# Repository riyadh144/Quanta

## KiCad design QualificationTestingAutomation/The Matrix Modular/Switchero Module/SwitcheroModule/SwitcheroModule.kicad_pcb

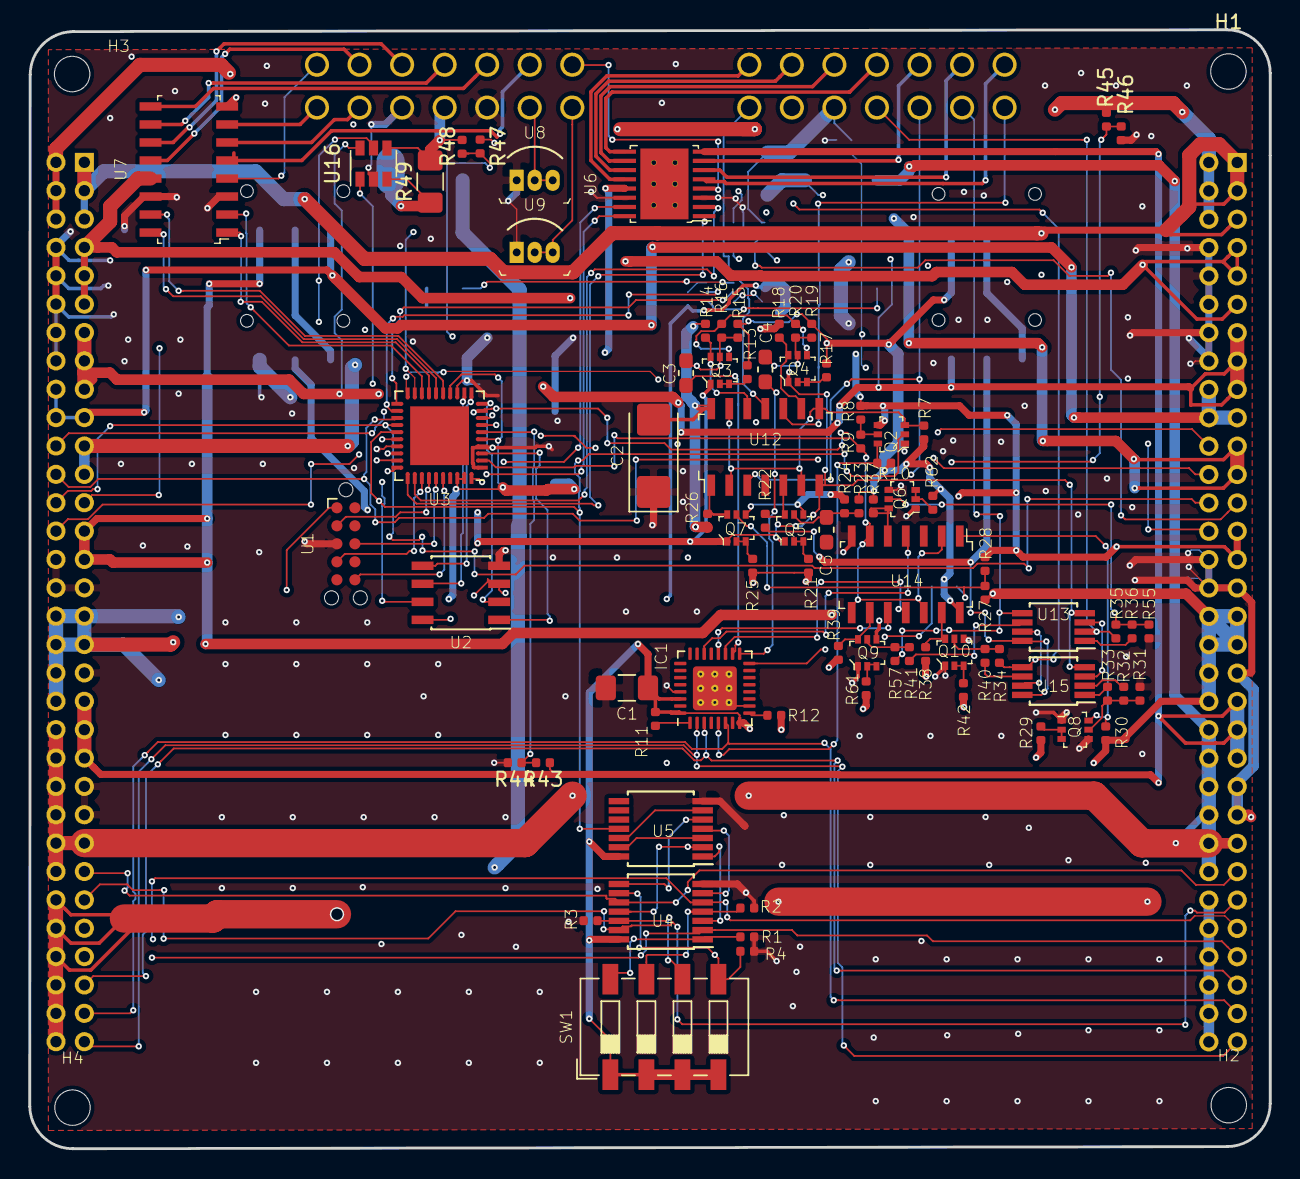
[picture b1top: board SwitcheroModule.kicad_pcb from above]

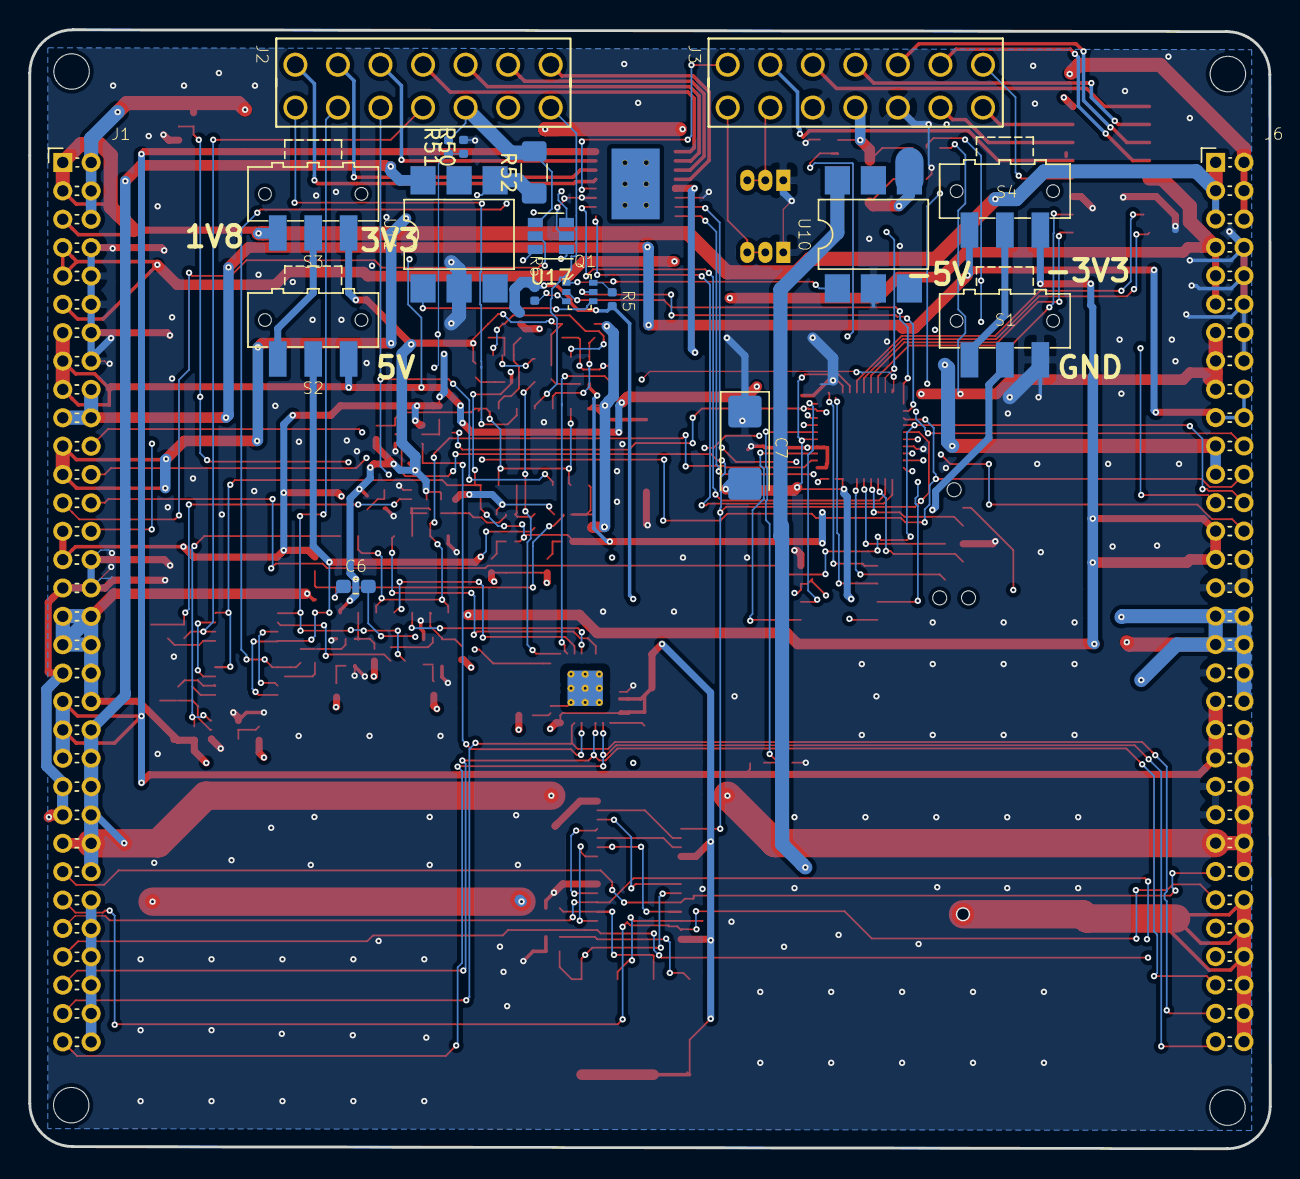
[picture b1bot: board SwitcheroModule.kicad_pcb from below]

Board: 4 copper layers, 87.5 x 78.9 mm, 104 parts (19 on the bottom side), 139 nets.

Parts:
C1: .1uF; C_1206_3216Metric_Pad1.42x1.75mm_HandSolder
C2, C7: 1uF; CP_EIA-6032-15_Kemet-U_Pad2.25x2.35mm_HandSolder
C3, C4, C5, C6: 1uF; C_0603_1608Metric_Pad1.05x0.95mm_HandSolder
H1, H2, H3, H4: MountingHole; MountingHole_2.5mm
IC1: MAX3109ETJ+; QFN-32-1EP_5x5mm_P0.5mm_EP3.1x3.1mm_ThermalVias
J1, J6: Conn_02x32_Counter_Clockwise_MountingPin; PinHeader_2x32_P2.00mm_VerticalOpp
J2, J3: OBD Connector; 3MM
Q1, Q2, Q3, Q4, Q5, Q6, Q7, Q8, Q9, Q10: 2N7002DW; SOT-363
R1, R2, R3, R4, R29, R30, R37, R38, R39, R42, R45, R61, R62: 100k; R_0402_1005Metric
R5, R6: 8K; R_0402_1005Metric
R7, R8, R9, R10, R12: 100K; R_0402_1005Metric
R11: 10K; R_0402_1005Metric
R13, R17, R21, R25: 15K; R_0402_1005Metric
R14, R18, R22, R26: 15k; R_0402_1005Metric
R15, R16, R19, R20, R23, R24, R27, R28: 200K; R_0402_1005Metric
R31, R55: RESISTOR; R_0402_1005Metric
R32, R33, R34, R35, R36, R40, R41, R57: R0; R_0402_1005Metric
R43, R48, R51: 1meg; R_0402_1005Metric
R44, R47, R50: 40K; R_0402_1005Metric
R46: 23.8K; R_0402_1005Metric
R49, R52: .02; R_1206_3216Metric_Pad1.42x1.75mm_HandSolder
S1, S2, S3, S4: ATE1D-2M3-10-Z; SW_SPDT_CK-JS102011SAQN
SW1: SW_DIP_x04; SW_DIP_SPSTx04_Slide_6.7x11.72mm_W6.73mm_P2.54mm_LowProfile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
U1: TC2050-JTAG-SchematicAutomation-rescue; Tag-Connect_TC2050-IDC-NL_2x05_P1.27mm_Vertical
U2: AT25SF081-SSHD-X; SOIC-8_3.9x4.9mm_P1.27mm
U3: MSP430G2755IRHA40; Texas_S-PVQFN-N40_EP4.15x4.15mm
U4: SN74HC266DR; TSSOP-14_4.4x5mm_P0.65mm
U5: SN74LVC08APWR; TSSOP-14_4.4x5mm_P0.65mm
U6: MAX14752; TSSOP-16-1EP_W4.40mm
U7: DG408LE; SOIC-16_W3.90mm
U8, U9: DS18B20_; TO-92-3
U10, U11: TLP3546; SMDIP-6_W7.62mm
U12, U14: CD4070B; SOIC-14_W3.9mm
U13, U15: MAX324CUA; MSOP-8_3x3mm_P0.65mm
U16, U17: INA181; SOT-23-6

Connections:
1.25V: J1.25, J6.25, U16.5, U17.5
1_ADC0: J3.14, U6.4
1_ADC1: J2.12, U6.7
1_ADC2: J2.13, U6.6
1_ADC3: J2.14, U6.5
1_CTS: J2.3, U12.3
1_GarminPWR: J2.5, R51.2, R52.2, U17.4
1_GarminRX: J2.6, R34.1, U15.5
1_GarminTX: J2.7, U12.11
1_IN0: J2.8, U6.12
1_IN1: J2.9, U6.11
1_IN2: J2.10, U6.10
1_IN3: J2.11, U6.9
1_OUT0: J3.8, U7.4
1_OUT1: J3.13, U7.5
1_OUT2: J3.6, U7.6
1_OUT3: J3.7, U7.7
1_OWB_PRI: J3.2, U8.2, U8.3
1_OWB_SEC: J3.1, U9.2, U9.3
1_RTS: J2.4, R35.2, U13.2
1_RX: J2.2, R57.1, U13.5
1_TX: J2.1, U12.10
1_Vin: J3.4, R48.2, R49.2, U16.4
2_OUT0: J3.9, U7.12
2_OUT1: J3.10, U7.11
2_OUT2: J3.11, U7.10
2_OUT3: J3.12, U7.9
+1V8: J1.1, J1.3, J1.5, J6.1, J6.3, J6.5, S3.3
+2V5: J1.28, J6.28, U3.28
+3V3: C1.1, C7.2, IC1.8, IC1.30, IC1.32, J1.33, J1.34, J1.35, J1.36, J1.38, J1.40, J6.33, J6.34, J6.35, J6.36, J6.38, J6.40, R5.1, R6.1, R7.1, R10.1, R11.2, R12.2, R13.1, R15.1, R17.1, R19.1, R21.1, R23.1, R25.1, R27.1, R29.1, R30.2, R37.2, R38.2, R39.2, R42.1, R61.1, R62.1, S3.1, SW1.1, SW1.2, SW1.3, SW1.4, U1.1, U2.3, U2.8, U3.5, U3.14, U3.38, U3.39, U4.14, U5.14, U14.14
+5V: J1.13, J1.15, J1.17, J6.13, J6.15, J6.17, S2.1, U16.6, U17.6
+12V: J1.7, J1.9, J1.11, J6.7, J6.9, J6.11, U7.13
+VSW: C2.2, R14.2, R18.2, R22.2, R26.2, S2.2, U12.14, U13.8, U15.8
-3V3: J1.27, J1.29, J6.27, J6.29, Q2.4, Q3.4, Q4.4, Q5.4, Q7.4, R8.2, R16.2, R20.2, R24.2, R28.2, S4.1
-5V: J1.18, J1.19, J1.20, J6.18, J6.19, J6.20, S4.3
-VSW: Q3.1, Q4.1, Q5.1, Q7.1, S1.2, U12.7, U13.4, U15.4
/Micro/CSB: U2.1, U3.3
/Micro/SCKB: U2.6, U3.12
/Micro/SIMOB: U2.5, U3.11
/Micro/SOMIB: U2.2, U3.10
/Micro/TCK: U1.4, U3.33
/Micro/TDI: U1.8, U3.35
/Micro/TDO: U1.6, U3.36
/Micro/TMS: U1.2, U3.34
/Micro/\HOLD: U2.7, U3.40
/Serial/RX/Sheet5CA21CAA/TX_+3v3-3v3: Q3.6, R14.1, U12.12
/Serial/RX/TX_3v3_1: C3.2, IC1.18
/Serial/RX/TX_3v3_2: C4.2, IC1.17
/Serial/RX/TX_3v3_3: C6.2, IC1.16
/Serial/RX/sheet5CA23CF1/TX_+3v3-3v3: Q4.6, R18.1, U12.9
/Serial/RX/sheet5CA2401A/TX_+3v3-3v3: Q5.6, R22.1, U12.5
/Serial/RX/sheet5CA24179/TX_+3v3-3v3: Q7.6, R26.1, U12.1
/Serial/sheet5C94ECE6/RX_1: R32.2, U15.2
/Serial/sheet5C94ECE6/RX_3V3_2: IC1.22, U14.4
/Serial/sheet5C94ECE6/RX_3V3_3: IC1.20, U14.10
/Serial/sheet5C94ECE6/RX_3V3_4: IC1.19, U14.11
CTS_CONT: U13.3, U15.3
GND: C1.2, C2.1, C7.1, IC1.10, IC1.29, IC1.33, J1.8, J1.10, J1.12, J1.14, J1.16, J1.30, J1.31, J1.32, J1.37, J1.45, J1.47, J3.3, J3.5, J6.8, J6.10, J6.12, J6.14, J6.16, J6.30, J6.31, J6.32, J6.37, J6.45, J6.47, Q2.1, Q6.1, Q6.4, Q8.1, Q8.4, Q9.1, Q9.4, Q10.1, Q10.4, R1.2, R2.2, R3.2, R4.2, R31.2, R44.2, R46.2, R47.2, R50.2, R55.2, S1.1, U1.3, U2.4, U3.1, U3.4, U3.13, U3.27, U4.7, U5.7, U6.3, U6.14, U7.3, U7.14, U8.1, U9.1, U10.2, U11.2, U14.7, U16.2, U17.2
HT: J1.21, J1.23, J6.21, J6.23, U6.13
IADC_Garmin: U3.19, U17.1
IADC_Vin: U3.8, U16.1
LO: J1.2, J1.4, J1.6, J6.2, J6.4, J6.6, R45.1, U7.8
MISO0: J1.24, J6.24, U3.23
MISO1: IC1.2, J1.63, J6.63
MOSI0: J1.26, J6.26, U3.24
MOSI1: IC1.6, J1.61, J6.61
MSP_MUX1_EN: U3.32, U6.2
MSP_MUX2_EN: U3.18, U7.2
MSP_MUXA: U3.17, U7.1
MSP_MUXB: U3.16, U7.16
MSP_MUXC: U3.15, U7.15
MSP_MUXD: U3.31, U6.1
MSP_MUXE: U3.30, U6.16
MSP_MUXF: U3.29, U6.15
MSP_REL_1: Q1.2, U3.21
MSP_REL_2: Q1.5, U3.22
unnamed: C3.1, Q3.5, R15.2, R16.1
unnamed: C4.1, Q4.5, R19.2, R20.1
unnamed: C5.1, Q5.5, R23.2, R24.1
unnamed: C6.1, Q7.5, R27.2, R28.1
unnamed: IC1.1, R11.1
unnamed: IC1.9, R12.1
unnamed: Q1.1, U10.1
unnamed: Q1.3, R6.2
unnamed: Q1.4, U11.1
unnamed: Q1.6, R5.2
unnamed: Q2.5, R8.1, R9.1
unnamed: Q3.2, Q3.3, R13.2
unnamed: Q4.2, Q4.3, R17.2
unnamed: Q5.2, Q5.3, R21.2
unnamed: Q6.2, Q6.3, R62.2
unnamed: Q6.5, R35.1, R36.1, R55.1
unnamed: Q6.6, R37.1, U14.5
unnamed: Q7.2, Q7.3, R25.2
unnamed: Q8.2, Q8.3, R29.2
unnamed: Q8.5, R31.1, R32.1, R33.1
unnamed: Q8.6, R30.1, U14.1
unnamed: Q9.2, Q9.3, R61.2
unnamed: Q9.5, R41.2, R57.2
unnamed: Q9.6, R39.1, U14.9
unnamed: Q10.2, Q10.3, R42.2
unnamed: Q10.5, R34.2, R40.2
unnamed: Q10.6, R38.1, U14.13
unnamed: R1.1, SW1.8, U4.1
unnamed: R2.1, SW1.7, U4.4
unnamed: R3.1, SW1.6, U4.12
unnamed: R4.1, SW1.5, U4.9
unnamed: R33.2, U15.1
unnamed: R36.2, U13.1
unnamed: R40.1, U15.6
unnamed: R41.1, U13.6
unnamed: R49.1, U10.4, U16.3
unnamed: R52.1, U11.4, U17.3
unnamed: S1.3, S4.2
unnamed: S2.3, S3.2
unnamed: U4.3, U5.1
unnamed: U4.6, U5.4
unnamed: U4.8, U5.5
unnamed: U4.11, U5.2
unnamed: U5.6, U5.12
unnamed: U5.3, U5.13
RS232INV: R9.2, U3.2, U14.2, U14.6, U14.8, U14.12
RS232INVDif: Q2.3, R7.2, U12.2, U12.6, U12.8, U12.13
S0: J1.57, J6.57, U4.2
S1: J1.55, J6.55, U4.5
S2: J1.53, J6.53, U4.13
S3: J1.51, J6.51, U4.10
SCLK0: J1.22, J6.22, U3.9
SCLK1: IC1.3, J1.59, J6.59
SS: Q2.2, U3.25, U5.11
SSINV: IC1.5, Q2.6, R10.2
TX_CONT: U13.7, U15.7
VAA: J1.39, J1.41, J1.43, J6.39, J6.41, J6.43, R43.1, U6.8
VADC_Garmin: R50.1, R51.1, U3.20
VADC_LO: R45.2, R46.1, U3.7
VADC_VAA: R43.2, R44.1, U3.6
VADC_Vin: R47.1, R48.1, U3.26
VD: J1.42, J1.44, J1.46, J1.48, J1.49, J1.50, J1.52, J6.42, J6.44, J6.46, J6.48, J6.49, J6.50, J6.52, U11.6
VDC: J1.54, J1.56, J1.58, J1.60, J1.62, J1.64, J6.54, J6.56, J6.58, J6.60, J6.62, J6.64, U10.6

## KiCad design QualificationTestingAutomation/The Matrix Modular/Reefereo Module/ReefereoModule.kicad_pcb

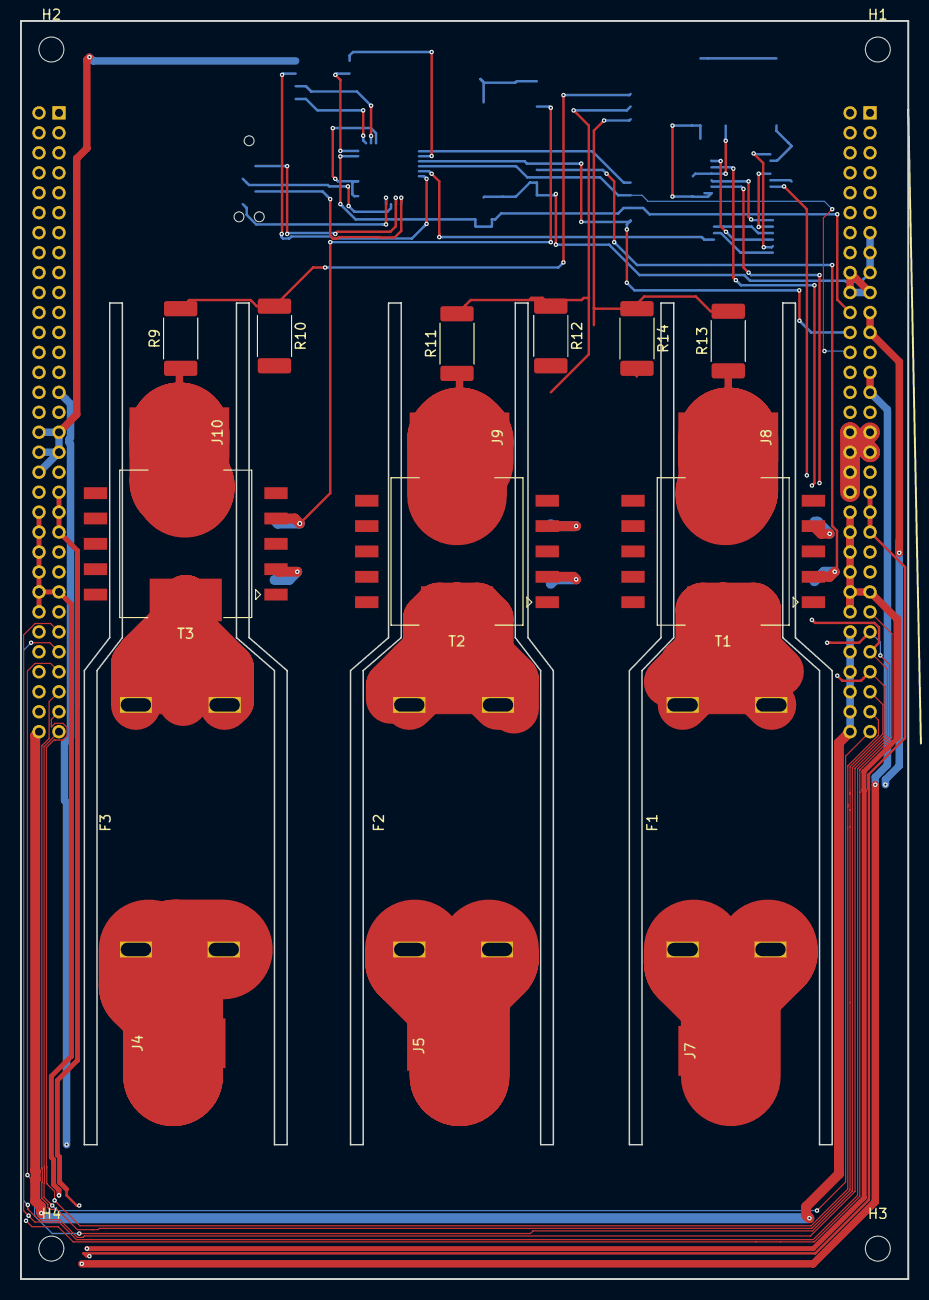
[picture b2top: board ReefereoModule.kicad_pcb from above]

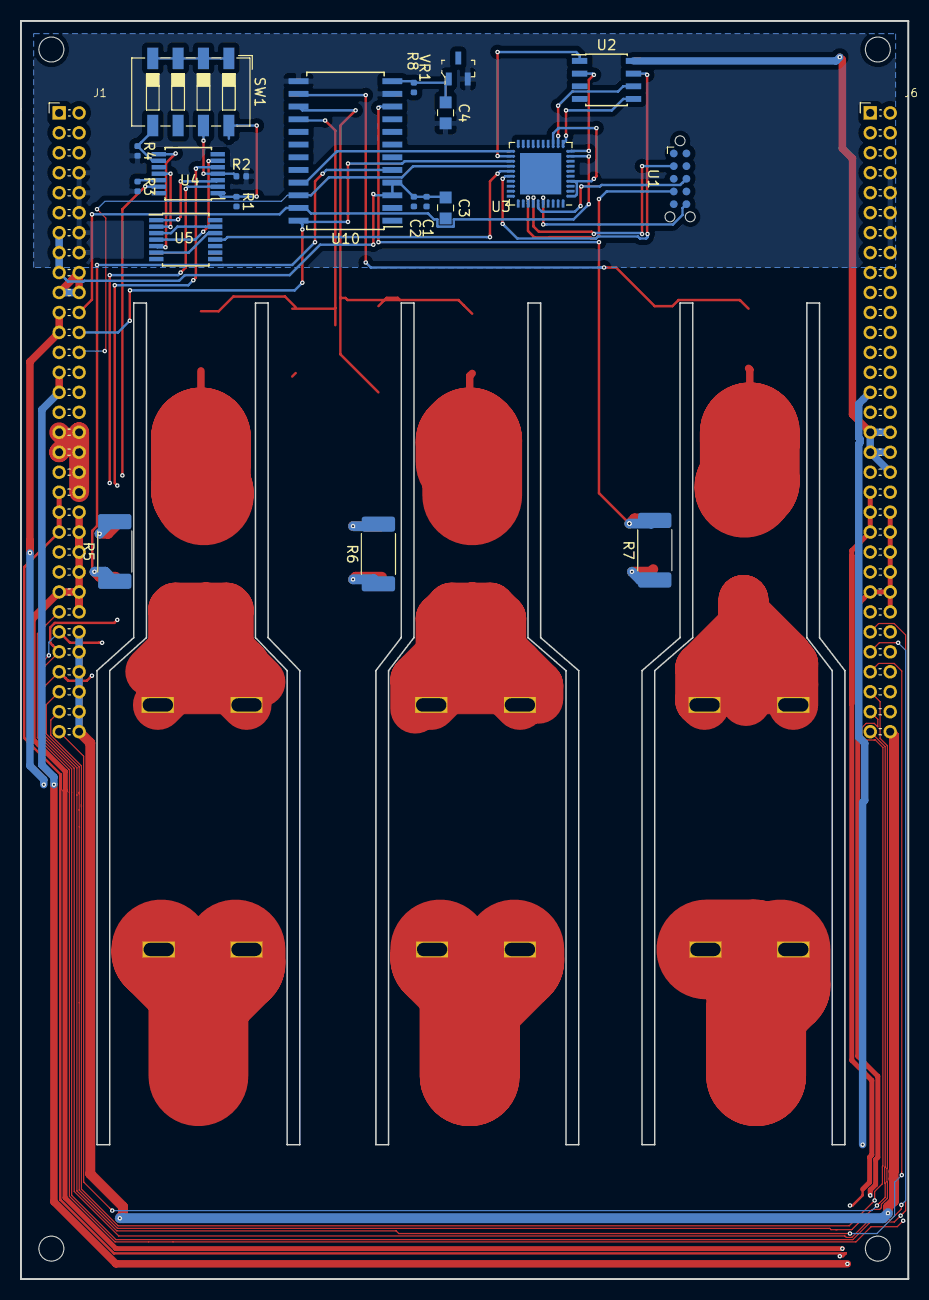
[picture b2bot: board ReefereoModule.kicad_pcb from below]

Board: 4 copper layers, 88.9 x 126.0 mm, 44 parts (22 on the bottom side), 65 nets.

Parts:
C1: 100pF; C_0402_1005Metric
C2: 100nF; C_0402_1005Metric
C3: 10uF; 0805
C4: 1uF; 0805
F1, F2, F3: Fuse; 0606LittleFuse
H1, H2, H3, H4: MountingHole; MountingHole_2.5mm
J1, J6: Conn_02x32_Counter_Clockwise_MountingPin; PinHeader_2x32_P2.00mm_VerticalOpp
J4, J5, J7, J8, J9, J10: Conn_01x01_Female; SolderWirePad_1x01_SMD_5x10mm
R1, R2, R3, R4: 100k; R_0402_1005Metric
R5, R6, R7: YAG5136CT-ND; R_2512_6332Metric_Pad1.52x3.35mm_HandSolder
R8: 1K; C_0402_1005Metric
R9, R11, R13: R_US; R_2512_6332Metric_Pad1.52x3.35mm_HandSolder
R10, R12, R14: 5K; R_2512_6332Metric_Pad1.52x3.35mm_HandSolder
SW1: SW_DIP_x04; SW_DIP_SPSTx04_Slide_6.7x11.72mm_W6.73mm_P2.54mm_LowProfile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
T1, T2, T3: CST2010_Split; Transformer_Coilcraft_CST2010
U1: TC2050-JTAG-SchematicAutomation-rescue; Tag-Connect_TC2050-IDC-NL_2x05_P1.27mm_Vertical
U2: AT25SF081-SSHD-X; SOIC-8_3.9x4.9mm_P1.27mm
U3: MSP430G2755IRHA40; Texas_S-PVQFN-N40_EP4.15x4.15mm
U4: SN74HC266DR; TSSOP-14_4.4x5mm_P0.65mm
U5: SN74LVC08APWR; TSSOP-14_4.4x5mm_P0.65mm
U10: ADE7758; SOIC-24W_7.5x15.4mm_P1.27mm
VR1: LM4040D25FTA; SOT-23-3

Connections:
1.25V: J1.25, J6.25
+1V8: J1.1, J1.3, J1.5, J6.1, J6.3, J6.5
+2V5: J1.28, J6.28
+3V3: J1.33, J1.34, J1.35, J1.36, J1.38, J1.40, J6.33, J6.34, J6.35, J6.36, J6.38, J6.40, R8.1, SW1.1, SW1.2, SW1.3, SW1.4, U1.1, U2.3, U2.8, U3.5, U3.14, U3.38, U3.39
+5V: C1.1, C2.1, C3.1, J1.13, J1.15, J1.17, J6.13, J6.15, J6.17, U10.3, U10.4
+12V: J1.7, J1.9, J1.11, J6.7, J6.9, J6.11
-3V3: J1.27, J1.29, J6.27, J6.29
-5V: J1.18, J1.19, J1.20, J6.18, J6.19, J6.20
/ADE7758/PAIN: F3.2, T3.11
/ADE7758/PAOUT: J8.1, R13.1, T1.12
/ADE7758/PAS: R13.2, R14.1, U10.16
/ADE7758/PBIN: F2.2, T2.11
/ADE7758/PBOUT: J9.1, R11.1, T2.12
/ADE7758/PBS: R11.2, R12.1, U10.15
/ADE7758/PCIN: F1.2, T1.11
/ADE7758/PCOUT: J10.1, R9.1, T3.12
/ADE7758/PCS: R9.2, R10.1, U10.14
/Micro/CSB: U2.1, U3.22
/Micro/SCKB: U2.6, U3.12
/Micro/SIMOB: U2.5, U3.11
/Micro/SOMIB: U2.2, U3.10
/Micro/SS: U3.25, U5.11
/Micro/TCK: U1.4, U3.33
/Micro/TDI: U1.8, U3.35
/Micro/TDO: U1.6, U3.36
/Micro/TMS: U1.2, U3.34
/Micro/\HOLD: U2.7, U3.26
CSADE: U3.21, U10.21
GND: C1.2, C2.2, C3.2, C4.2, J1.8, J1.10, J1.12, J1.14, J1.16, J1.30, J1.31, J1.32, J1.37, J1.45, J1.47, J6.8, J6.10, J6.12, J6.14, J6.16, J6.30, J6.31, J6.32, J6.37, J6.45, J6.47, R1.2, R2.2, R3.2, R4.2, R10.2, R12.2, R14.2, U1.3, U2.4, U10.2, U10.11, U10.13, VR1.2
HT: J1.21, J1.23, J6.21, J6.23
LO: J1.2, J1.4, J1.6, J6.2, J6.4, J6.6
MISO0: J1.24, J6.24, U3.23, U10.24
MISO1: J1.63, J6.63
MOSI0: J1.26, J6.26, U3.24, U10.22
MOSI1: J1.61, J6.61
unnamed: C4.1, R8.2, U10.12, VR1.1
unnamed: F1.1, J7.1
unnamed: F2.1, J5.1
unnamed: F3.1, J4.1
unnamed: R1.1, SW1.8, U4.1
unnamed: R2.1, SW1.7, U4.4
unnamed: R3.1, SW1.6, U4.12
unnamed: R4.1, SW1.5, U4.9
unnamed: R5.1, T1.2, U10.5
unnamed: R5.2, T1.4, U10.6
unnamed: R6.1, T2.2, U10.7
unnamed: R6.2, T2.4, U10.8
unnamed: R7.1, T3.2, U10.9
unnamed: R7.2, T3.4, U10.10
unnamed: U3.1, U3.4, U3.13
unnamed: U4.3, U5.1
unnamed: U4.6, U5.4
unnamed: U4.8, U5.5
unnamed: U4.11, U5.2
unnamed: U5.6, U5.12
unnamed: U5.3, U5.13
S0: J1.57, J6.57, U4.2
S1: J1.55, J6.55, U4.5
S2: J1.53, J6.53, U4.13
S3: J1.51, J6.51, U4.10
SCLK0: J1.22, J6.22, U3.9, U10.23
SCLK1: J1.59, J6.59
VAA: J1.39, J1.41, J1.43, J6.39, J6.41, J6.43
VD: J1.42, J1.44, J1.46, J1.48, J1.49, J1.50, J1.52, J6.42, J6.44, J6.46, J6.48, J6.49, J6.50, J6.52
VDC: J1.54, J1.56, J1.58, J1.60, J1.62, J1.64, J6.54, J6.56, J6.58, J6.60, J6.62, J6.64

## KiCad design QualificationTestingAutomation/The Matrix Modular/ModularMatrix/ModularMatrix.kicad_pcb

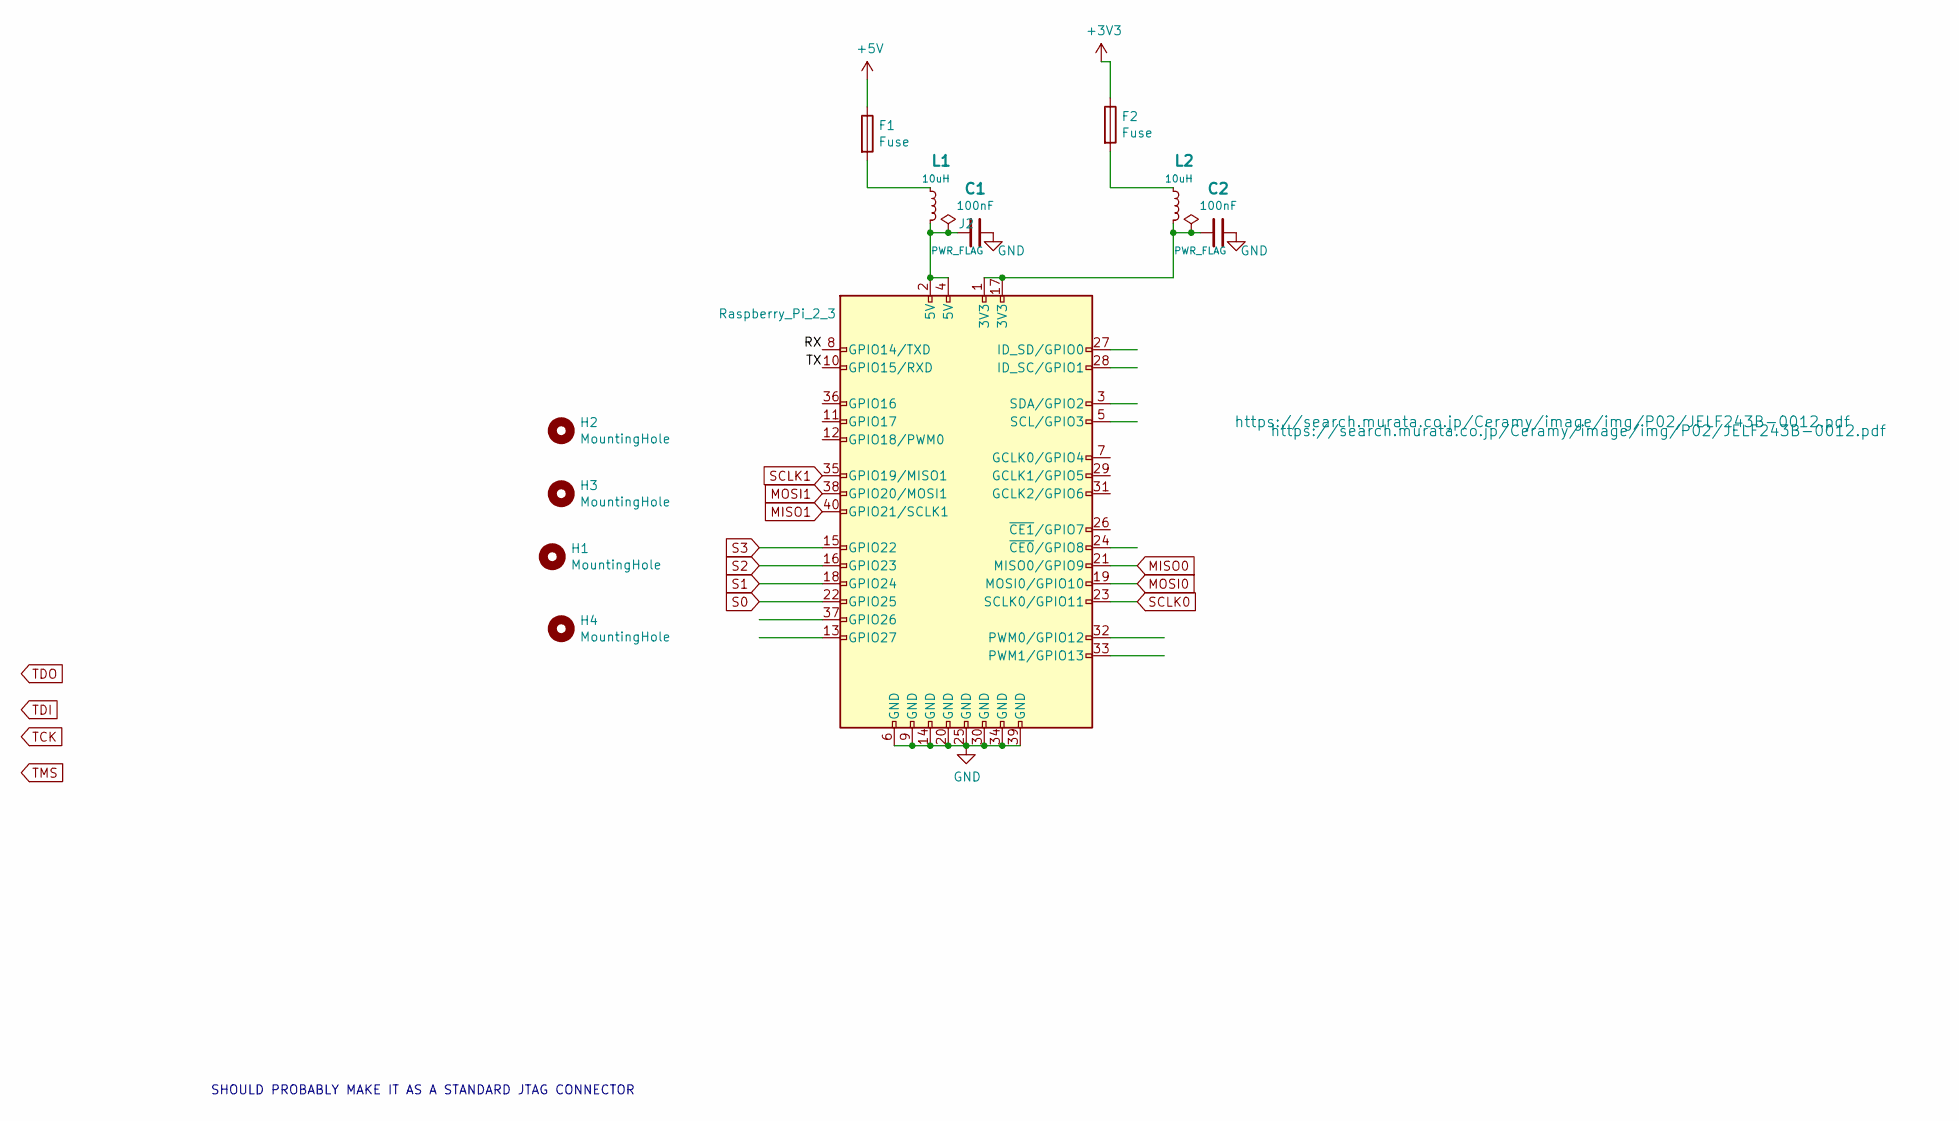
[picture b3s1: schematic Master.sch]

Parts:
C1, C2: 100nF; C_0402_1005Metric
F1, F2: Fuse; Fuse_1206_3216Metric_Pad1.42x1.75mm_HandSolder
H1, H2, H3, H4: MountingHole; MountingHole_2.5mm
J2: Raspberry_Pi_2_3; PinSocket_2x20_P2.54mm_Vertical_SMD
L1, L2: 10uH; 0805; PART 490-4025-1-ND

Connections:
+3V3: F2.1; also elsewhere on the board
+5V: F1.1; also elsewhere on the board
/Master/RX: J2.8 (GPIO14/TXD)
/Master/TX: J2.10 (GPIO15/RXD)
MISO0: J2.21 (MISO0/GPIO9); also elsewhere on the board
MISO1: J2.40 (GPIO21/SCLK1); also elsewhere on the board
MOSI0: J2.19 (MOSI0/GPIO10); also elsewhere on the board
MOSI1: J2.38 (GPIO20/MOSI1); also elsewhere on the board
unnamed: C1.1, J2.2 (5V), J2.4 (5V), L1.2
unnamed: C2.1, J2.1 (3V3), J2.17 (3V3), L2.2
unnamed: F1.2, L1.1
unnamed: F2.2, L2.1
S0: J2.22 (GPIO25); also elsewhere on the board
S1: J2.18 (GPIO24); also elsewhere on the board
S2: J2.16 (GPIO23); also elsewhere on the board
S3: J2.15 (GPIO22); also elsewhere on the board
SCLK0: J2.23 (SCLK0/GPIO11); also elsewhere on the board
SCLK1: J2.35 (GPIO19/MISO1); also elsewhere on the board

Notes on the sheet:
SHOULD PROBABLY MAKE IT AS A STANDARD JTAG CONNECTOR

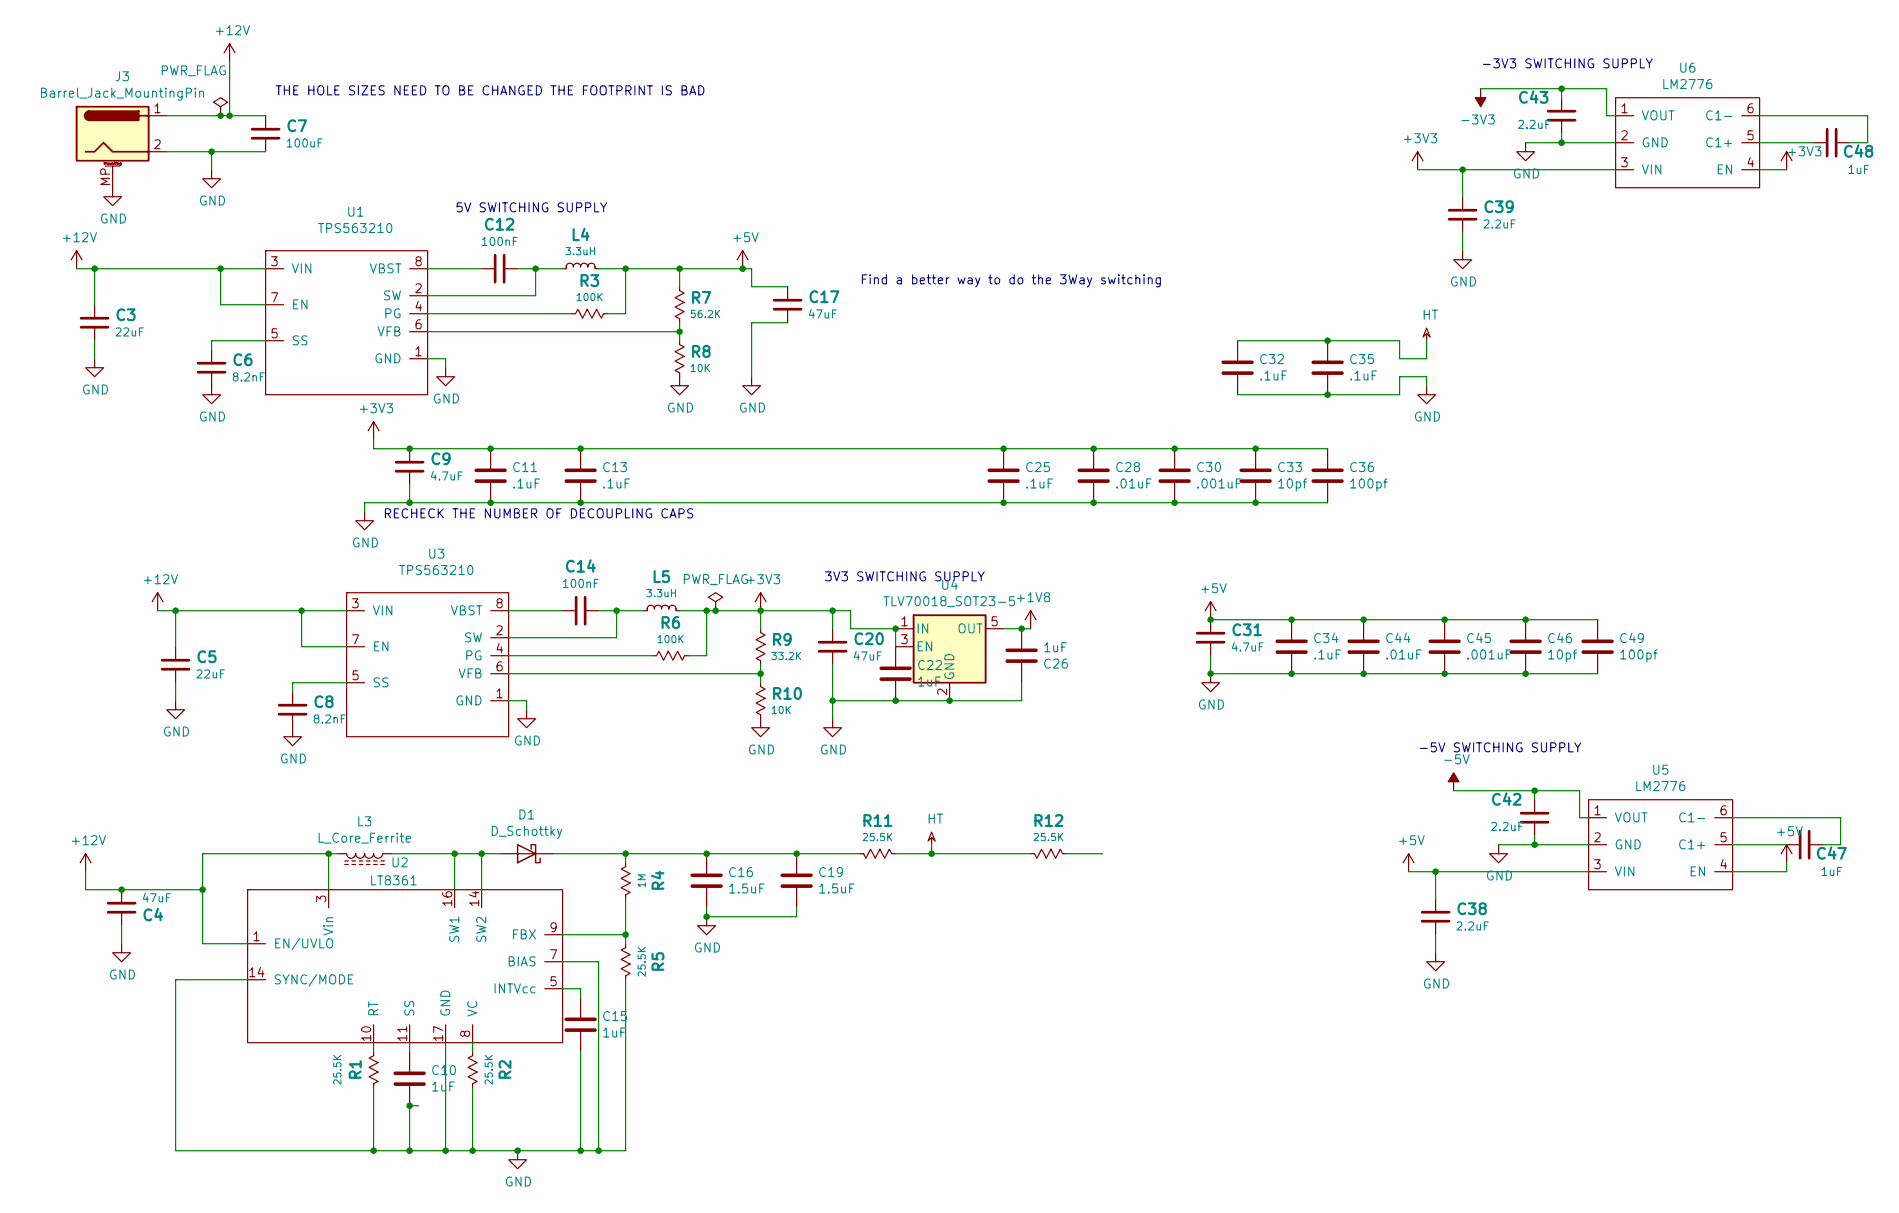
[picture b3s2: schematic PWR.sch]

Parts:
C3: 22uF; C_0402_1005Metric
C4: 47uF; C_1210_3225Metric_Pad1.42x2.65mm_HandSolder
C5: 22uF; C_1206_3216Metric_Pad1.42x1.75mm_HandSolder
C6, C8: 8.2nF; C_0402_1005Metric
C7: 100uF; C_1210_3225Metric_Pad1.42x2.65mm_HandSolder
C9, C31: 4.7uF; C_1206_3216Metric_Pad1.42x1.75mm_HandSolder
C10: 1uF; C_0402_1005Metric
C11, C13: .1uF; C_0603_HandSoldering
C12, C14: 100nF; C_0402_1005Metric
C15: 1uF; C_0603_1608Metric_Pad1.05x0.95mm_HandSolder
C16, C19: 1.5uF; C_1206_3216Metric_Pad1.42x1.75mm_HandSolder
C17, C20: 47uF; C_1206_3216Metric_Pad1.42x1.75mm_HandSolder
C22, C26, C47, C48: 1uF; C_1206_3216Metric_Pad1.42x1.75mm_HandSolder
C25, C34: .1uF; C_0402_1005Metric
C28, C44: .01uF; C_0402_1005Metric
C30, C45: .001uF; C_0402_1005Metric
C32, C35: .1uF; C_1206_3216Metric_Pad1.42x1.75mm_HandSolder
C33, C46: 10pf; C_0402_1005Metric
C36, C49: 100pf; C_0402_1005Metric
C38, C39, C42, C43: 2.2uF; C_0805_2012Metric
D1: D_Schottky; D_PowerDI-123; MPN DFLS2100
J3: Barrel_Jack_MountingPin; BarrelJack_CUI_PJ-063AH_Horizontal; Digi-Key_PN CP-037A-ND
L3: L_Core_Ferrite; L_Wuerth_WE-PD-Typ-LS_Handsoldering; MPN WE-PD 1280 74477006
L4, L5: 3.3uH; 0805
R1, R2, R5: 25.5K; R_0402_1005Metric
R3, R6: 100K; R_0402_1005Metric
R4: 1M; R_0805_2012Metric_Pad1.15x1.40mm_HandSolder
R7: 56.2K; R_0402_1005Metric
R8, R10: 10K; R_0402_1005Metric
R9: 33.2K; R_0402_1005Metric
R11: 25.5K; R_1210_3225Metric_Pad1.42x2.65mm_HandSolder
R12: 25.5K; R_1210_3225Metric
U1, U3: TPS563210; SOT-23-8_Handsoldering
U2: LT8361; MSOP-12-16-1EP_3x4mm_P0.5mm_EP1.65x2.85mm; MPN LT8361IMSE#PBF
U4: TLV70018_SOT23-5; SOT-23-5
U5, U6: LM2776; SOT-23-6

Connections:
+1V8: C26.2, U4.5 (OUT); also elsewhere on the board
+3V3: C9.2, C11.1, C13.1, C20.1, C22.1, C25.1, C28.1, C30.1, C33.1, C36.1, C39.2, L5.2, R6.2, R9.1, U4.1 (IN), U4.3 (EN), U6.3 (VIN), U6.4 (EN); also elsewhere on the board
+5V: C17.1, C31.2, C34.1, C38.2, C44.1, C45.1, C46.1, C49.1, L4.2, R3.2, R7.1, U5.3 (VIN), U5.4 (EN); also elsewhere on the board
+12V: C3.1, C4.2, C5.1, C7.1, J3.1, L3.2, U1.3 (VIN), U1.7 (EN), U2.1 (EN/UVLO), U2.3 (Vin), U3.3 (VIN), U3.7 (EN); also elsewhere on the board
-3V3: C43.2, U6.1 (VOUT); also elsewhere on the board
-5V: C42.2, U5.1 (VOUT); also elsewhere on the board
HT: C32.1, C35.1, R11.1, R12.2; also elsewhere on the board
unnamed: C6.2, U1.5 (SS)
unnamed: C8.2, U3.5 (SS)
unnamed: C10.1, U2.11 (SS)
unnamed: C12.1, L4.1, U1.2 (SW)
unnamed: C12.2, U1.8 (VBST)
unnamed: C14.1, L5.1, U3.2 (SW)
unnamed: C14.2, U3.8 (VBST)
unnamed: C15.1, U2.5 (INTVcc)
unnamed: C16.1, C19.1, D1.1 (K), R4.2, R11.2
unnamed: C47.1, U5.5 (C1+)
unnamed: C47.2, U5.6 (C1-)
unnamed: C48.1, U6.5 (C1+)
unnamed: C48.2, U6.6 (C1-)
unnamed: R1.2, U2.10 (RT)
unnamed: R2.2, U2.8 (VC)
unnamed: R3.1, U1.4 (PG)
unnamed: R4.1, R5.2, U2.9 (FBX)
unnamed: R6.1, U3.4 (PG)
unnamed: R7.2, R8.1, U1.6 (VFB)
unnamed: R9.2, R10.1, U3.6 (VFB)

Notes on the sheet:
5V SWITCHING SUPPLY
3V3 SWITCHING SUPPLY
-3V3 SWITCHING SUPPLY
RECHECK THE NUMBER OF DECOUPLING CAPS
Find a better way to do the 3Way switching
THE HOLE SIZES NEED TO BE CHANGED THE FOOTPRINT IS BAD
-5V SWITCHING SUPPLY

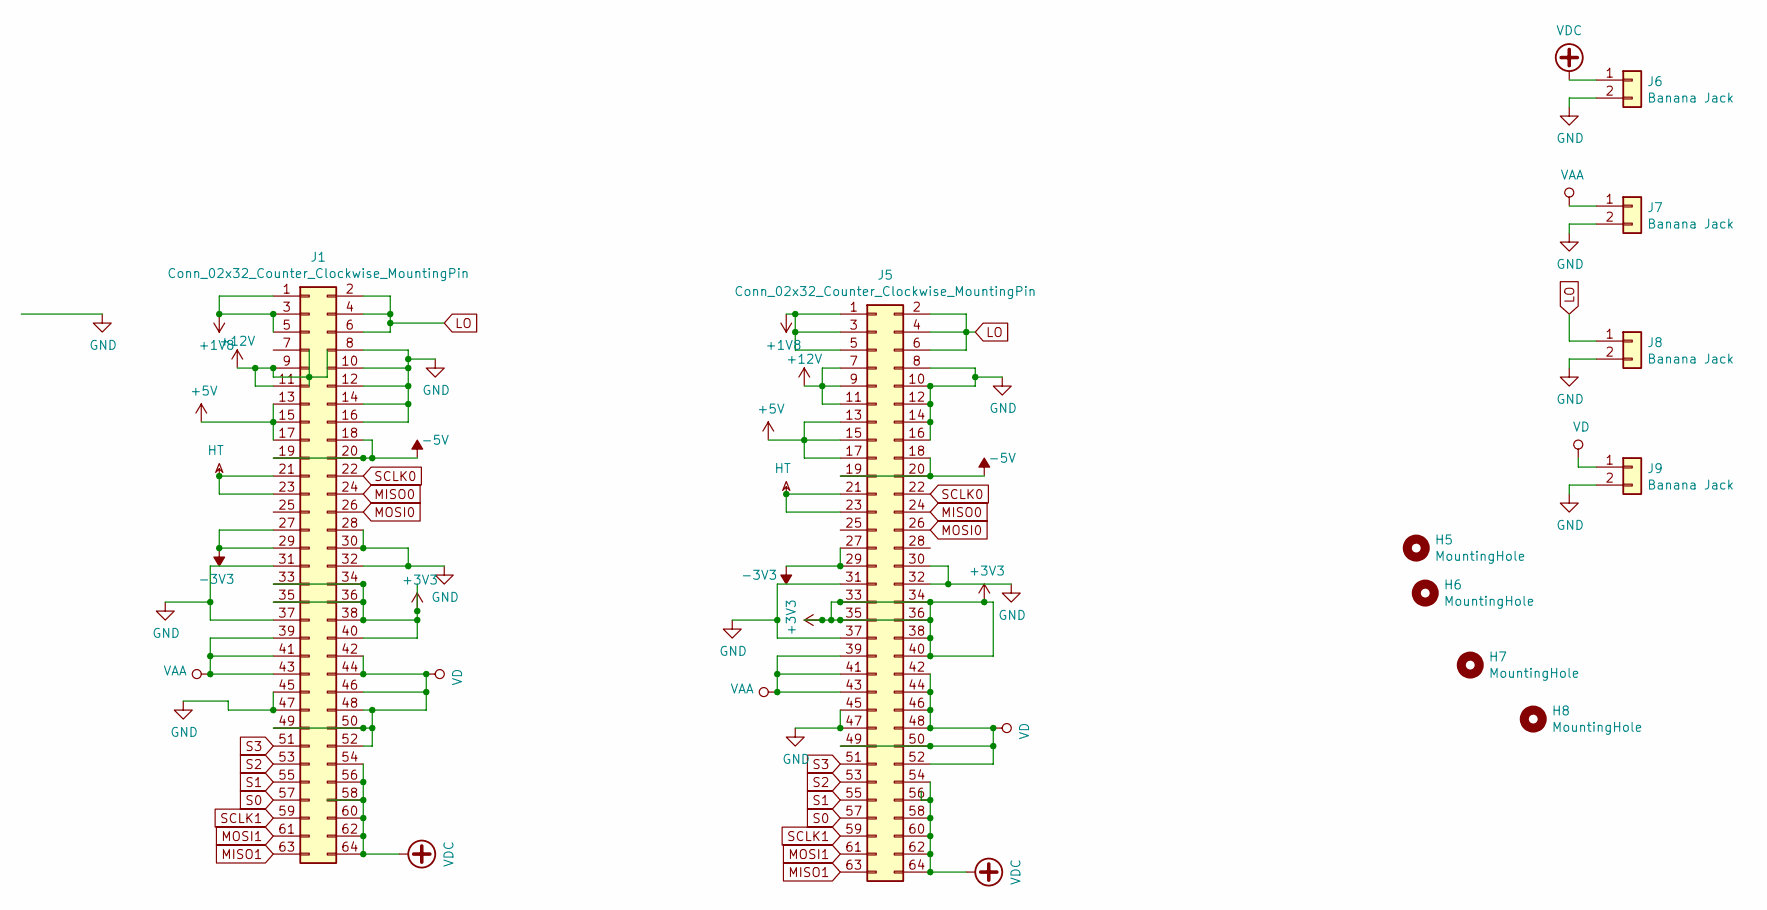
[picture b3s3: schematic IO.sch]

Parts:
H5, H6, H7, H8: MountingHole; MountingHole_2.5mm
J1, J5: Conn_02x32_Counter_Clockwise_MountingPin; PinHeader_2x32_P2.00mm_Vertical_Clockwise
J6, J7, J8, J9: Banana Jack; Banana_Jack_2Pin_Standard_Spacing

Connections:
+1V8: J1.1, J1.3, J1.5, J5.1, J5.3, J5.5; also elsewhere on the board
+3V3: J1.33, J1.34, J1.35, J1.36, J1.38, J1.40, J5.33, J5.34, J5.35, J5.36, J5.38, J5.40; also elsewhere on the board
+5V: J1.13, J1.15, J1.17, J5.13, J5.15, J5.17; also elsewhere on the board
+12V: J1.9, J1.11, J5.7, J5.9, J5.11; also elsewhere on the board
-3V3: J1.27, J1.29, J5.27, J5.29; also elsewhere on the board
-5V: J1.18, J1.19, J1.20, J5.18, J5.19, J5.20; also elsewhere on the board
HT: J1.21, J1.23, J5.21, J5.23; also elsewhere on the board
LO: J1.2, J1.4, J1.6, J5.2, J5.4, J5.6, J8.1
MISO0: J1.24, J5.24; also elsewhere on the board
MISO1: J1.63, J5.63; also elsewhere on the board
MOSI0: J1.26, J5.26; also elsewhere on the board
MOSI1: J1.61, J5.61; also elsewhere on the board
S0: J1.57, J5.57; also elsewhere on the board
S1: J1.55, J5.55; also elsewhere on the board
S2: J1.53, J5.53; also elsewhere on the board
S3: J1.51, J5.51; also elsewhere on the board
SCLK0: J1.22, J5.22; also elsewhere on the board
SCLK1: J1.59, J5.59; also elsewhere on the board
VAA: J1.39, J1.41, J1.43, J5.39, J5.41, J5.43, J7.1
VD: J1.42, J1.44, J1.46, J1.48, J1.49, J1.50, J1.52, J5.42, J5.44, J5.46, J5.48, J5.49, J5.50, J5.52, J9.1
VDC: J1.54, J1.56, J1.58, J1.60, J1.62, J1.64, J5.54, J5.56, J5.58, J5.60, J5.62, J5.64, J6.1

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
